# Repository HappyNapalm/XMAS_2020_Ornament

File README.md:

# XMAS_2020_Ornament
A repo to hold the design files for my 2020 Ornament Project

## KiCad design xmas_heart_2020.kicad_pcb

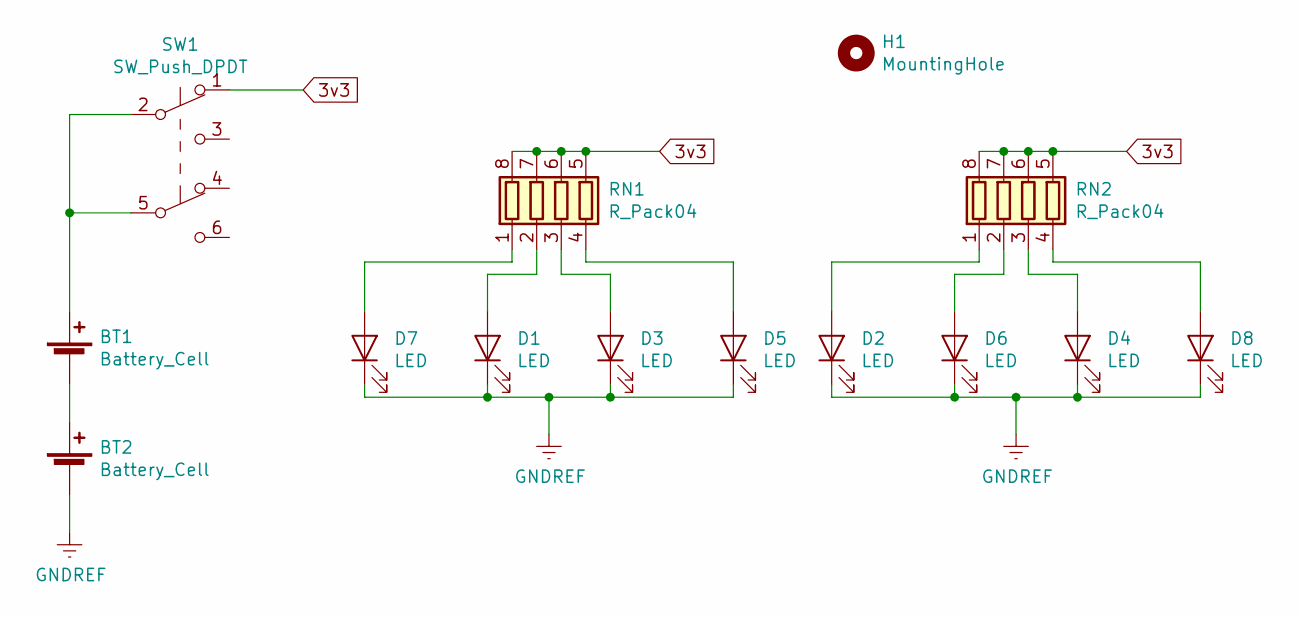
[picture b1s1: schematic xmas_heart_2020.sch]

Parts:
BT1, BT2: Battery_Cell; BHX1-LR44-SM
D1, D2, D3, D4, D5, D6, D7, D8: LED; LED_0603_1608Metric
H1: MountingHole; MountingHole_3mm
RN1, RN2: R_Pack04; R_Array_Concave_4x0603
SW1: SW_Push_DPDT; JS202011SCQN

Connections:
3v3: RN1.5 (R4.2), RN1.6 (R3.2), RN1.7 (R2.2), RN1.8 (R1.2), RN2.5 (R4.2), RN2.6 (R3.2), RN2.7 (R2.2), RN2.8 (R1.2), SW1.1 (A)
GNDREF: BT2.2 (-), D1.1 (K), D2.1 (K), D3.1 (K), D4.1 (K), D5.1 (K), D6.1 (K), D7.1 (K), D8.1 (K)
unnamed: BT1.1 (+), SW1.2 (B), SW1.5 (B)
unnamed: BT1.2 (-), BT2.1 (+)
unnamed: D1.2 (A), RN1.2 (R2.1)
unnamed: D2.2 (A), RN2.1 (R1.1)
unnamed: D3.2 (A), RN1.3 (R3.1)
unnamed: D4.2 (A), RN2.3 (R3.1)
unnamed: D5.2 (A), RN1.4 (R4.1)
unnamed: D6.2 (A), RN2.2 (R2.1)
unnamed: D7.2 (A), RN1.1 (R1.1)
unnamed: D8.2 (A), RN2.4 (R4.1)

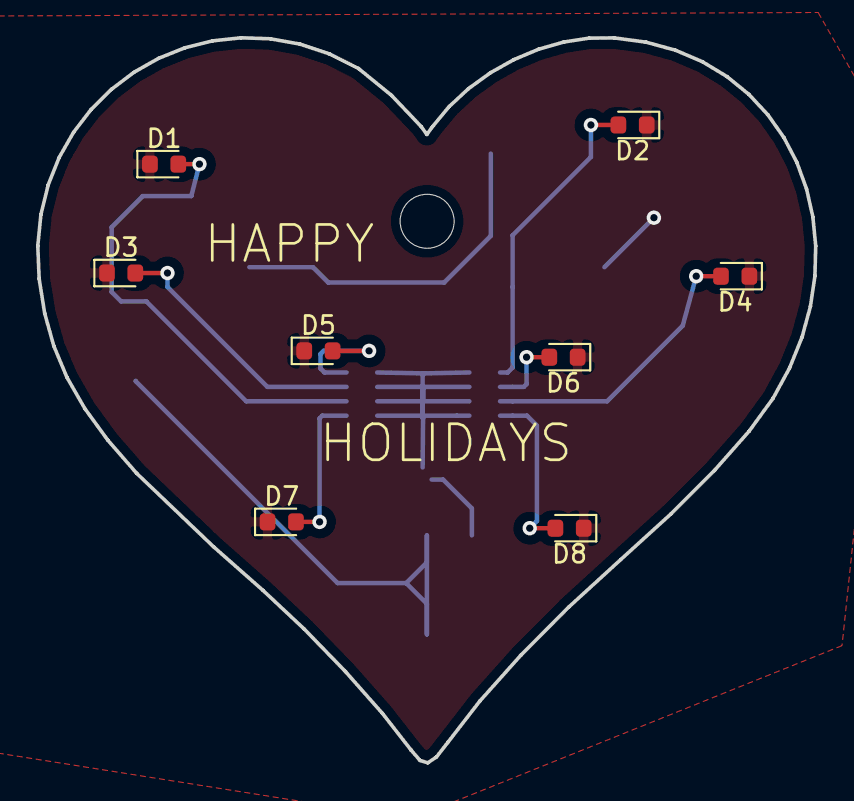
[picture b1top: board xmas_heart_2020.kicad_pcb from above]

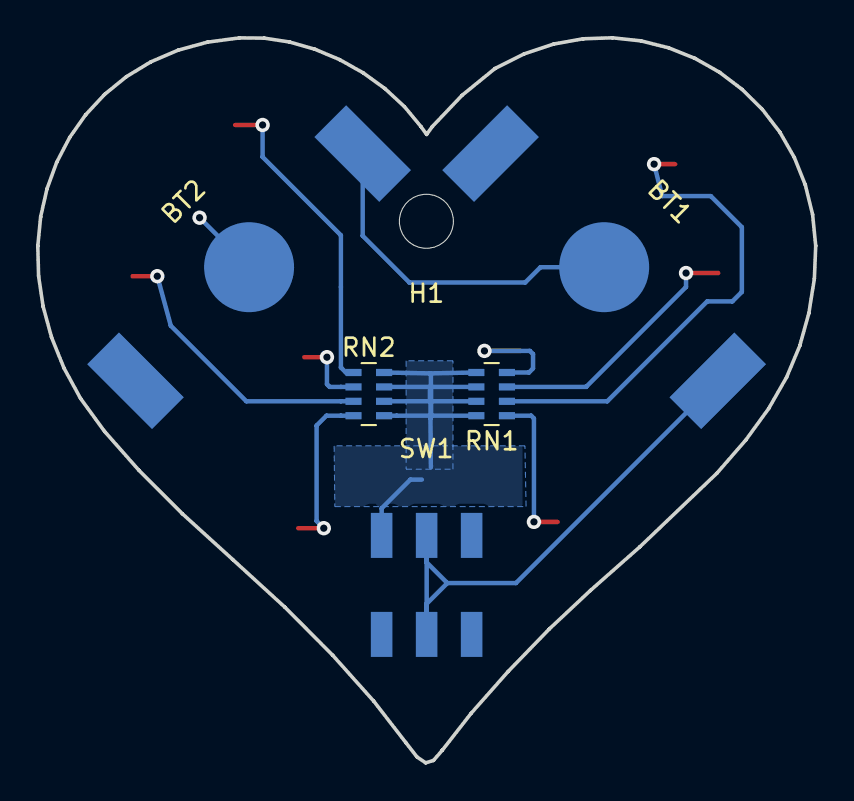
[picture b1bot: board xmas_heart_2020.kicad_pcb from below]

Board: 2 copper layers, 43.2 x 40.3 mm, 14 parts (6 on the bottom side), 12 nets.

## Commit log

2020-12-04 Uploading shipped info
2020-12-04 Adding BOM
